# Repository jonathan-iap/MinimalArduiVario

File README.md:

# MinimalArduiVario

A simple __variometer__.

It's a project based on an _"ATmega328p"_ and Software is written on ["Arduino langage"](https://www.arduino.cc/). But not with "Arduino IDE". For this I have used ["platformIO"](http://platformio.org/) with ["Atom"](https://atom.io/) as text editor.

Poject is initialised accordingly.
You can still compile and run program on "Arduino IDE"

Software is inspired by :  http://wildlab.org/index.php/2015/07/07/arduino-variometer/

For the Hardware, i use an ATmega328p, a cheap BMP180 sensor, a buzzer and a 3V coin cell. This is the minimal setup. For more flexibility i add three buttons. To set sensibility, volume and enable/disable falling detection.
A fourth button is added as on/off push button.

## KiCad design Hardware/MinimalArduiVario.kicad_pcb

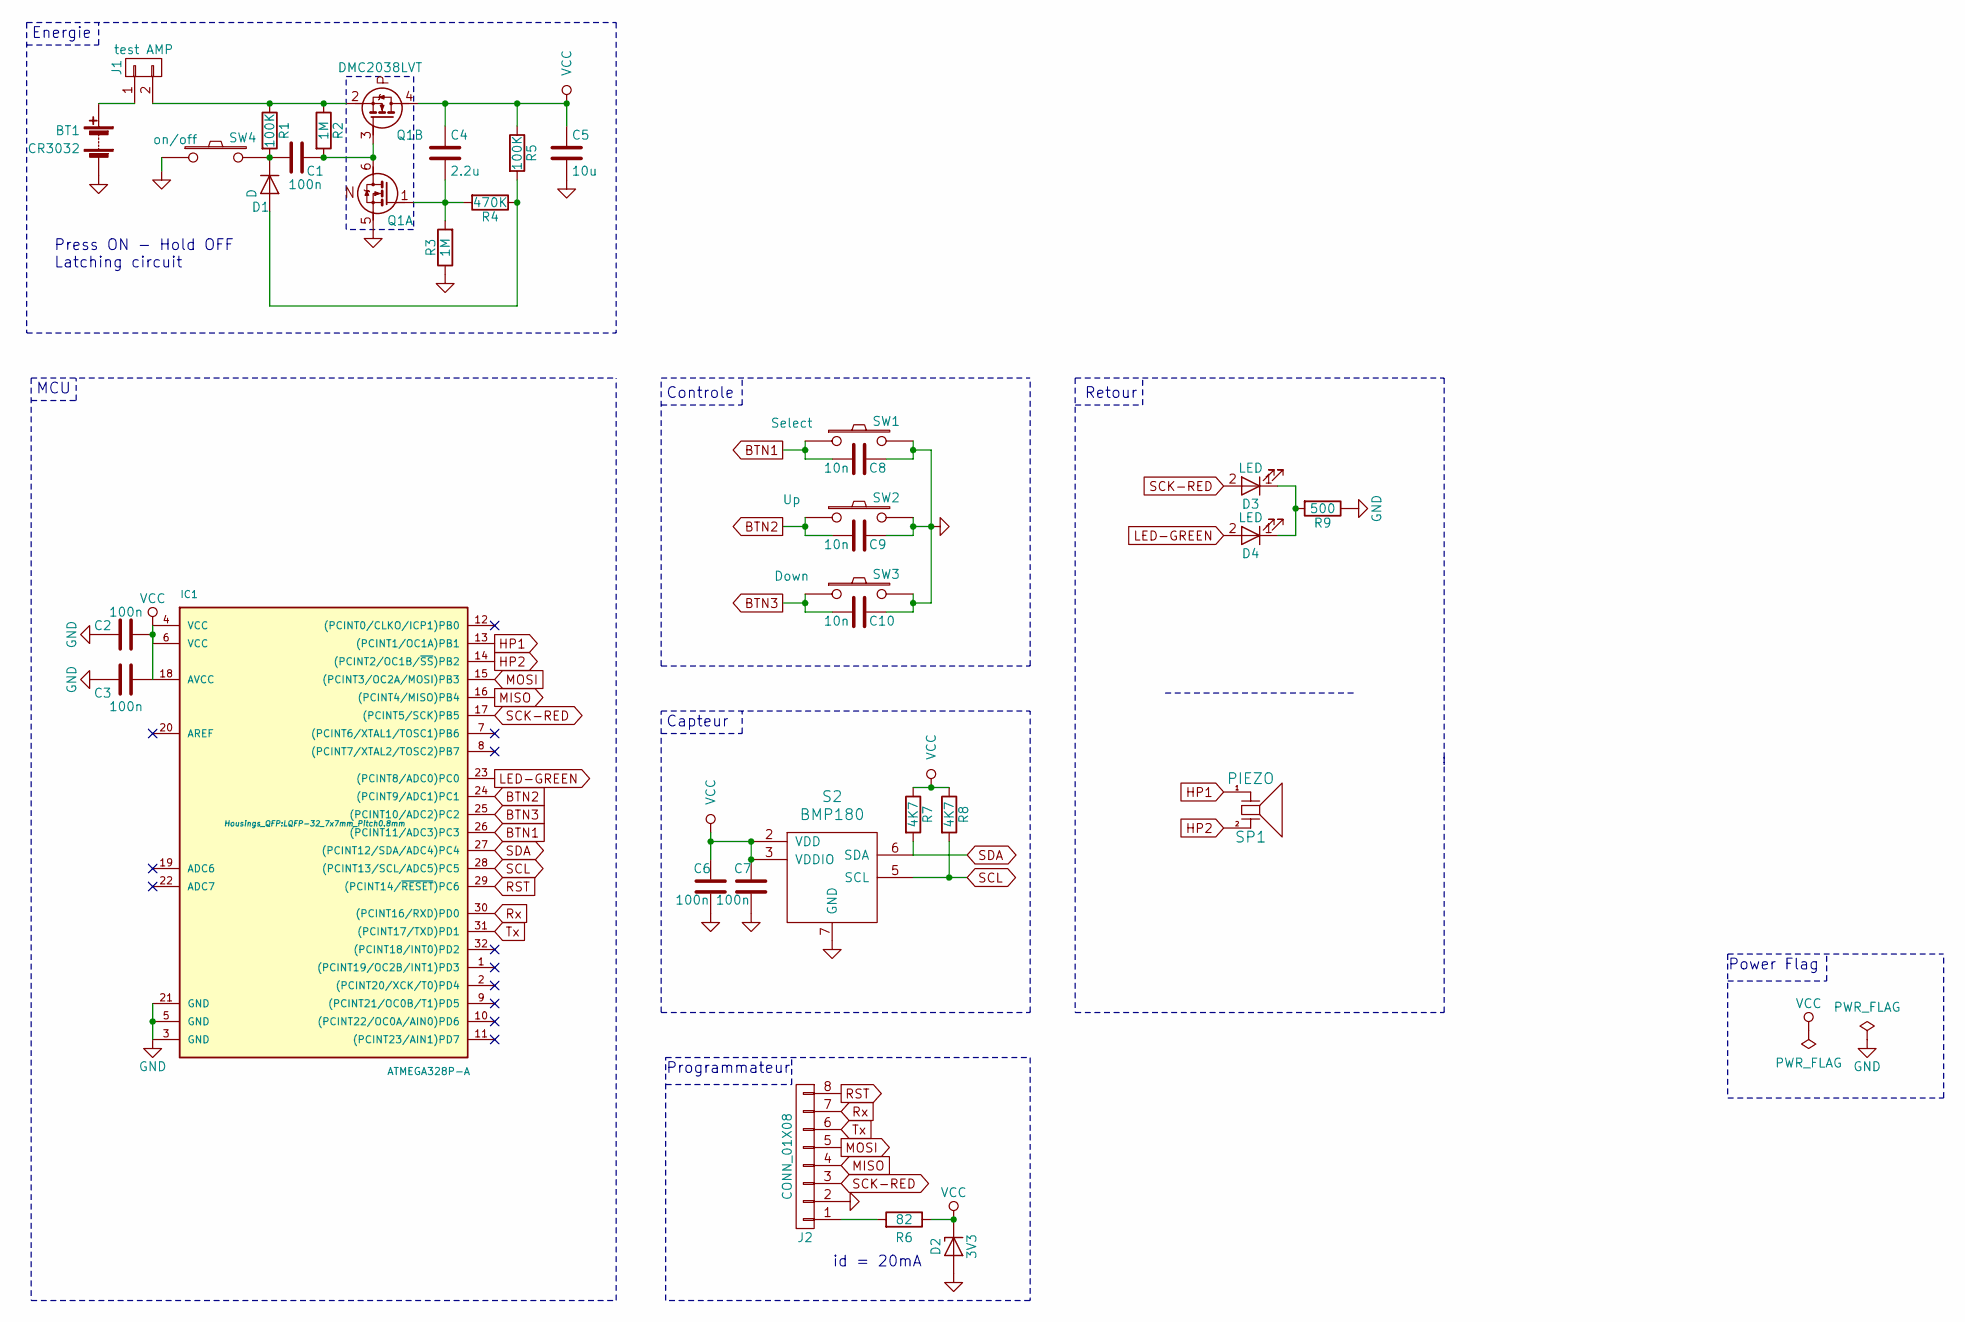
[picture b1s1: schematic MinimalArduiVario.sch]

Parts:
BT1: CR3032; Connector_SMD_x2
C1, C2, C3, C6, C7: 100n; C_0402
C4: 2.2u; C_0603
C5: 10u; C_0603
C8, C9, C10: 10n; C_0402
D1: D; D_SOD-123
D2: 3V3; D_SOD-123
D3, D4: LED; LED_D3.0mm
IC1: ATMEGA328P-A; LQFP-32_7x7mm_Pitch0.8mm
J1: test AMP; Pin_Header_Angled_1x02_Pitch2.54mm
J2: CONN_01X08; Pin_Header_Angled_1x08_Pitch2.54mm
Q1: DMC2038LVT; SOT-23-6
R1, R5: 100K; R_0402
R2, R3: 1M; R_0402
R4: 470K; R_0402
R6: 82; R_0402
R7, R8: 4K7; R_0402
R9: 500; R_0402
S2: BMP180
SP1: PIEZO; Connector_SMD_x2
SW1: Select; SW_Tactile_SPST_Angled
SW2: Up; SW_Tactile_SPST_Angled
SW3: Down; SW_Tactile_SPST_Angled
SW4: on/off; SW_Tactile_SPST_Angled

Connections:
BTN1: C8.2, IC1.26 ((PCINT11/ADC3)PC3), SW1.1
BTN2: C9.2, IC1.24 ((PCINT9/ADC1)PC1), SW2.1
BTN3: C10.2, IC1.25 ((PCINT10/ADC2)PC2), SW3.1
GND: BT1.2 (-), C2.1, C3.1, C5.2, C6.2, C7.2, C8.1, C9.1, C10.1, D2.2 (A), IC1.3 (GND), IC1.5 (GND), IC1.21 (GND), J2.2, Q1.5 (D2), R3.1, R9.1, S2.7 (GND), SW1.2, SW2.2, SW3.2, SW4.1
HP1: IC1.13 ((PCINT1/OC1A)PB1), SP1.1
HP2: IC1.14 ((PCINT2/OC1B/~SS~)PB2), SP1.2
LED-GREEN: D4.2 (A), IC1.23 ((PCINT8/ADC0)PC0)
MISO: IC1.16 ((PCINT4/MISO)PB4), J2.4
MOSI: IC1.15 ((PCINT3/OC2A/MOSI)PB3), J2.5
unnamed: BT1.1 (+), J1.1
unnamed: C1.1, Q1.3 (G2), Q1.6 (D2), R2.2
unnamed: C1.2, D1.1 (K), R1.2, SW4.2
unnamed: C4.2, Q1.1 (G2), R3.2, R4.2
unnamed: D1.2 (A), R4.1, R5.2
unnamed: D3.1 (K), D4.1 (K), R9.2
unnamed: J1.2, Q1.2 (D2), R1.1, R2.1
unnamed: J2.1, R6.2
RST: IC1.29 ((PCINT14/~RESET~)PC6), J2.8
Rx: IC1.30 ((PCINT16/RXD)PD0), J2.7
SCK-RED: D3.2 (A), IC1.17 ((PCINT5/SCK)PB5), J2.3
SCL: IC1.28 ((PCINT13/SCL/ADC5)PC5), R8.2, S2.5 (SCL)
SDA: IC1.27 ((PCINT12/SDA/ADC4)PC4), R7.2, S2.6 (SDA)
Tx: IC1.31 ((PCINT17/TXD)PD1), J2.6
VCC: C2.2, C3.2, C4.1, C5.1, C6.1, C7.1, D2.1 (K), IC1.4 (VCC), IC1.6 (VCC), IC1.18 (AVCC), Q1.4 (D2), R5.1, R6.1, R7.1, R8.1, S2.2 (VDD), S2.3 (VDDIO)

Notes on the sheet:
Energie
Programmateur
Power Flag
MCU
Controle
Retour
Capteur
Press ON - Hold OFF Latching circuit
id = 20mA

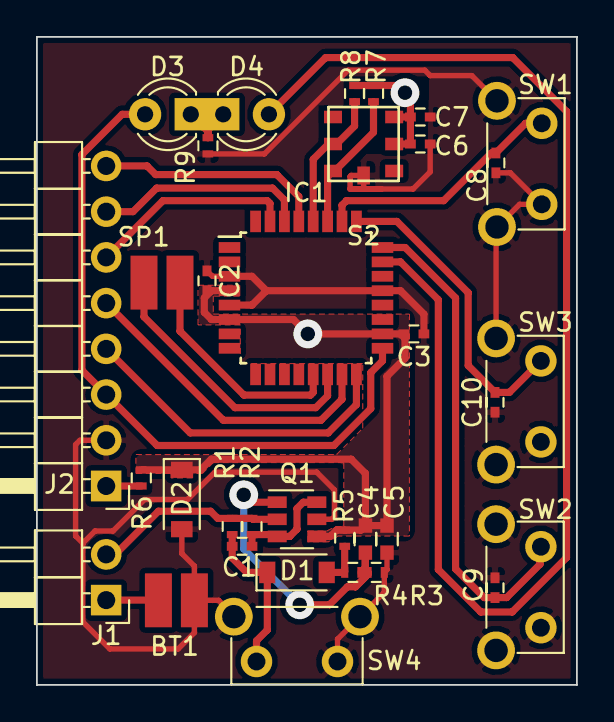
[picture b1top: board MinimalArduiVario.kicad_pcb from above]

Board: 2 copper layers, 30.0 x 36.0 mm, 34 parts (0 on the bottom side), 24 nets.

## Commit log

2017-05-06 Update schematic
2017-05-11 dev proto hardware v1
2017-05-26 Prepare dev software
    Change Adafruit lib for BMP180 and test all peripherals. Set fuses into "extra_script.py".
2017-05-27 Volume work, fix tone open/bloquing loop and change adafruit lib
2017-05-28 fix toneAC lib and add vario function
2017-06-01 Add menu function and set PWM_FREQ to 60Khz
2017-06-01 Set coefficient of variation
2017-06-02 adjust comments and add defines for filter setting
2017-06-03 Reinforce menu navigation, lower pwm freq, change brownout fuse
2017-06-03 add comments
2017-06-03 add void in function and correct variable type
2017-06-03 add author information
2017-06-03 remove pin arduino
2017-06-05 start 3D case
2017-06-05 Case ready to print
2017-06-10 > setting are usable <
2017-06-17 start power saving control
2017-06-18 add somes function to manage power
2017-06-19 actually usable !
